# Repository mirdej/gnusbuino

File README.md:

gnusbuino
=========

arduino compatible version of the gnusb - open source usb sensor box

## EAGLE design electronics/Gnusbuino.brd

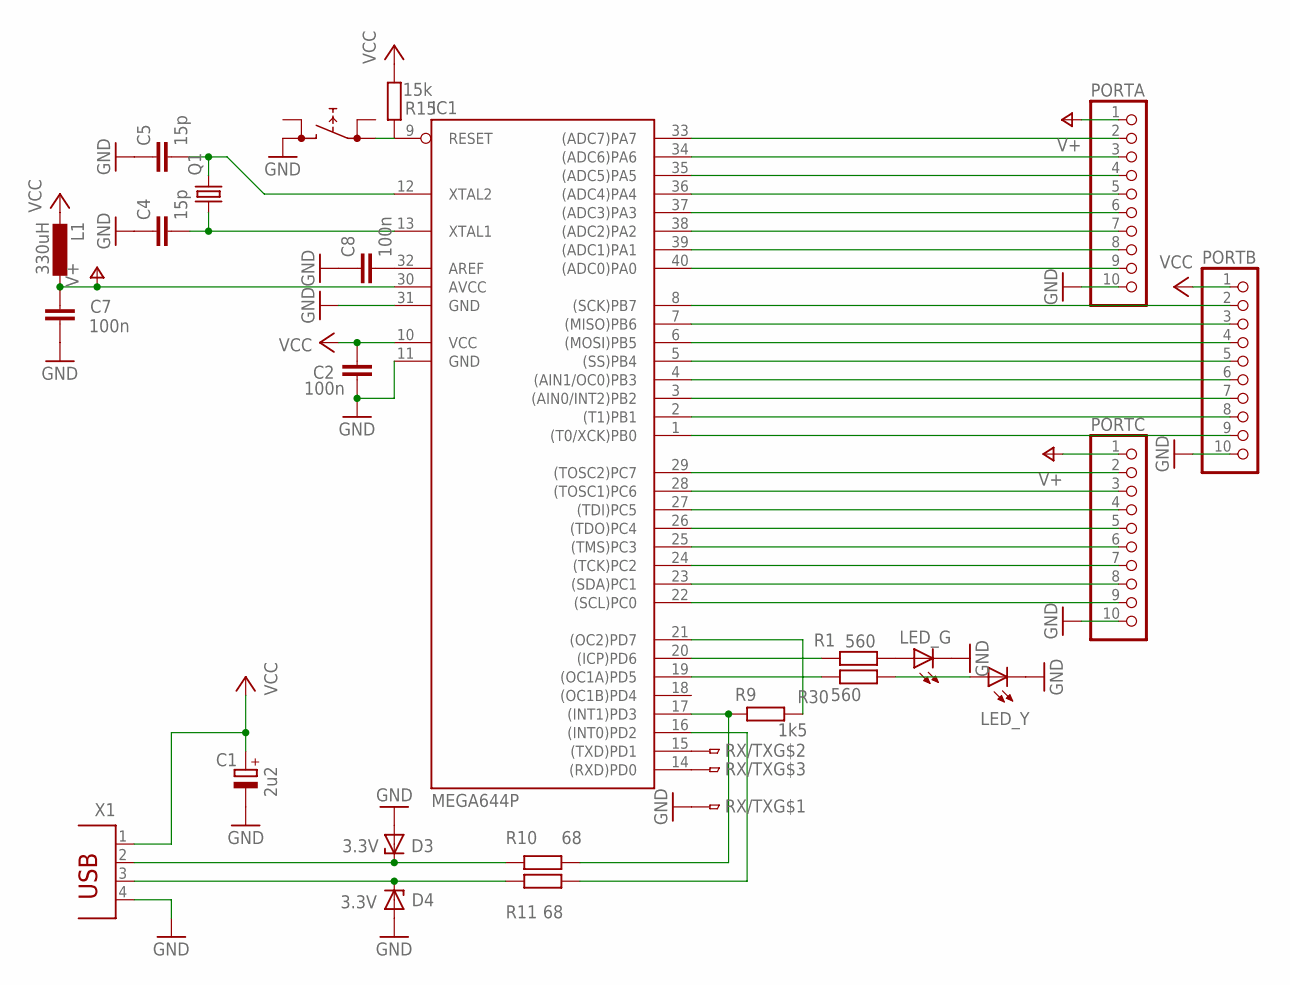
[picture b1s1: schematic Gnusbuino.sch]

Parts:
C1: 2u2; CT3528
C2, C7, C8: 100n; C0805
C4, C5: 15p; C1206
D3, D4: 3.3V; SOD80C
IC1: MEGA644P; DIL40
L1: 330uH; L1812
LED_G: LEDCHIPLED_1206; CHIPLED_1206
LED_Y: LEDCHIPLED_1206; CHIPLED_1206
PORTA: 10-PIN-SMD-2.54; 10PIN-SMD-2.54
PORTB: 10-PIN-SMD-2.54; 10PIN-SMD-2.54
PORTC: 10-PIN-SMD-2.54; 10PIN-SMD-2.54
Q1: CRYSTALHC49UP; HC49UP
R1, R30: 560; M1206
R9: 1k5; M1206
R10, R11: 68; M1206
R15: 15k; M1206
RESET: PRINTTASTER_SMD; SMD_SWITCH
RX/TX: 3PIN-SMD-2.54
X1: PN61729

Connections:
D+: D4.C, R11.1, X1.3
D-: D3.C, R10.1, X1.2
GND: C1.-, C2.2, C4.1, C5.1, C7.2, C8.1, D3.A, D4.A, IC1.11 (GND), IC1.31 (GND), LED_G.C, LED_Y.C, PORTA.10, PORTB.10, PORTC.10, RESET.BB (1), RX/TX.1, X1.4
MISO: IC1.7 ((MISO)PB6), PORTB.3
MOSI: IC1.6 ((MOSI)PB5), PORTB.4
unnamed: IC1.17 ((INT1)PD3), R9.2, R10.2
unnamed: IC1.9 (RESET), R15.1, RESET.AA (0)
unnamed: IC1.15 ((TXD)PD1), RX/TX.2
unnamed: IC1.14 ((RXD)PD0), RX/TX.3
unnamed: LED_G.A, R1.2
unnamed: C4.2, IC1.13 (XTAL1), Q1.1
unnamed: IC1.20 ((ICP)PD6), R1.1
unnamed: IC1.19 ((OC1A)PD5), R30.1
unnamed: LED_Y.A, R30.2
unnamed: C8.2, IC1.32 (AREF)
unnamed: IC1.33 ((ADC7)PA7), PORTA.2
unnamed: IC1.21 ((OC2)PD7), R9.1
unnamed: IC1.34 ((ADC6)PA6), PORTA.3
unnamed: IC1.35 ((ADC5)PA5), PORTA.4
unnamed: IC1.36 ((ADC4)PA4), PORTA.5
unnamed: IC1.37 ((ADC3)PA3), PORTA.6
unnamed: IC1.38 ((ADC2)PA2), PORTA.7
unnamed: IC1.39 ((ADC1)PA1), PORTA.8
unnamed: IC1.40 ((ADC0)PA0), PORTA.9
unnamed: IC1.4 ((AIN1/OC0)PB3), PORTB.6
unnamed: IC1.3 ((AIN0/INT2)PB2), PORTB.7
unnamed: IC1.2 ((T1)PB1), PORTB.8
unnamed: IC1.1 ((T0/XCK)PB0), PORTB.9
unnamed: IC1.16 ((INT0)PD2), R11.2
unnamed: IC1.29 ((TOSC2)PC7), PORTC.2
unnamed: IC1.28 ((TOSC1)PC6), PORTC.3
unnamed: IC1.27 ((TDI)PC5), PORTC.4
unnamed: IC1.26 ((TDO)PC4), PORTC.5
unnamed: IC1.25 ((TMS)PC3), PORTC.6
unnamed: IC1.24 ((TCK)PC2), PORTC.7
unnamed: IC1.23 ((SDA)PC1), PORTC.8
unnamed: IC1.22 ((SCL)PC0), PORTC.9
unnamed: C5.2, IC1.12 (XTAL2), Q1.2
SCK: IC1.8 ((SCK)PB7), PORTB.2
SS: IC1.5 ((SS)PB4), PORTB.5
V+: C7.1, IC1.30 (AVCC), L1.1, PORTA.1, PORTC.1
VCC: C1.+, C2.1, IC1.10 (VCC), L1.2, PORTB.1, R15.2, X1.1

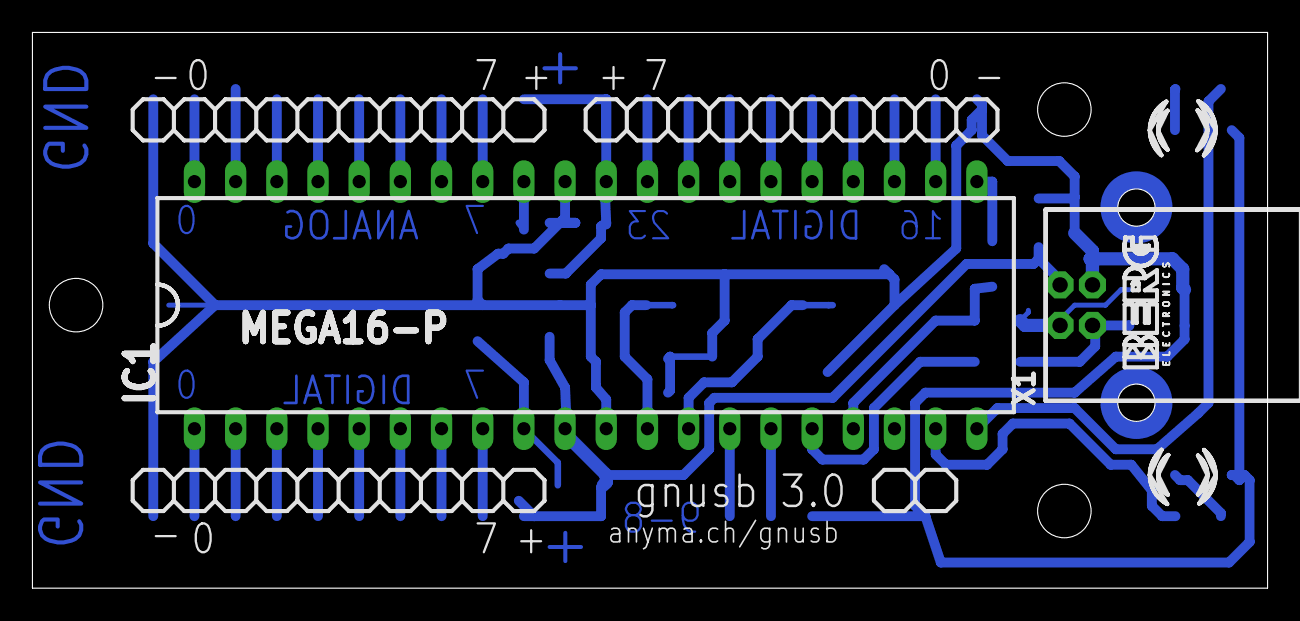
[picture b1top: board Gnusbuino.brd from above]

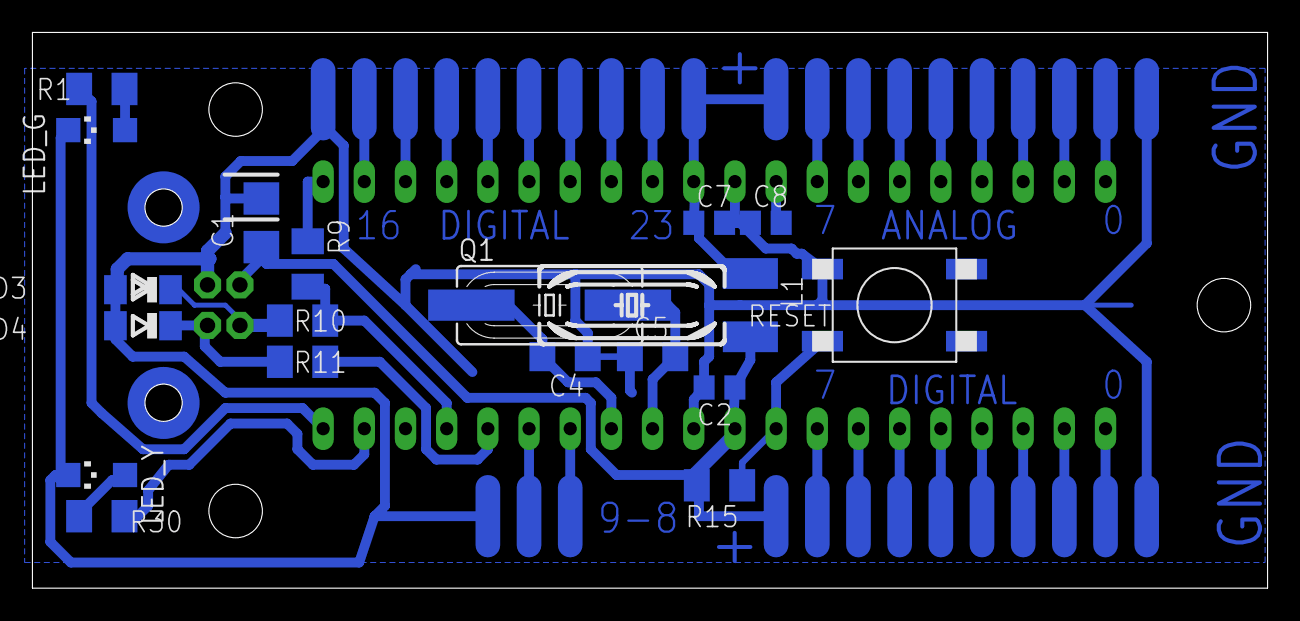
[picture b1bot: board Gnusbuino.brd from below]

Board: 2 copper layers, 76.2 x 34.3 mm, 25 parts (23 on the bottom side), 42 nets.

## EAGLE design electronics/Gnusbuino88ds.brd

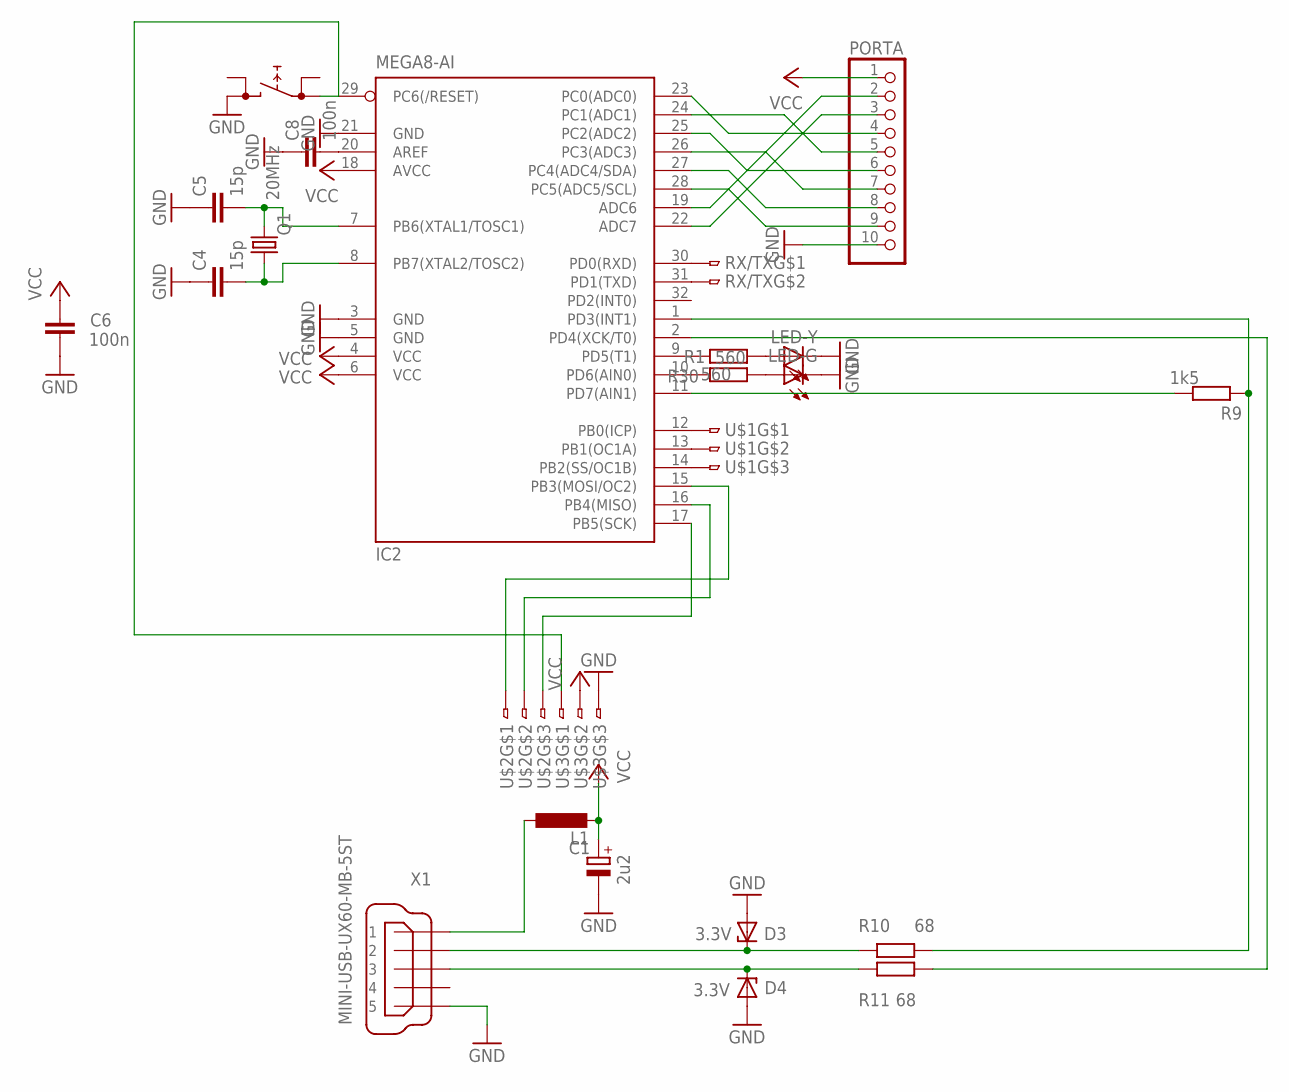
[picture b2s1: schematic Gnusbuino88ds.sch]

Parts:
C1: 2u2; CT3528
C4, C5: 15p; C1206
C6, C8: 100n; C0805
D3, D4: 3.3V; SOD80C
IC2: MEGA8-AI; TQFP32-08
L1: L-EUL3225M; L3225M
LED-G: LEDCHIPLED_1206; CHIPLED_1206
LED-Y: LEDCHIPLED_1206; CHIPLED_1206
PORTA: 10-PIN-SMD-2.54; 10PIN-SMD-2.54
Q1: 20MHz; HC49UP
R1, R30: 560; M1206
R9: 1k5; M1206
R10, R11: 68; M1206
RESET: PRINTTASTER_SMD; SMD_SWITCH
RX/TX: 3PIN-SMD-2.54
U$1, U$2, U$3: 3PIN-SMD-2.54
X1: MINI-USB-UX60-MB-5ST; UX60-MB-5ST

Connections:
D+: D4.C, R11.1, X1.3
D+1: IC2.2 (PD4(XCK/T0)), R11.2
D-: D3.C, R10.1, X1.2
GND: C1.-, C4.1, C5.1, C6.2, C8.1, D3.A, D4.A, IC2.3 (GND), IC2.5 (GND), IC2.21 (GND), LED-G.C, LED-Y.C, PORTA.10, RESET.BB (1), U$3.3, X1.5
unnamed: IC2.1 (PD3(INT1)), R9.2, R10.2
unnamed: IC2.29 (PC6(/RESET)), RESET.AA (0), U$3.1
unnamed: C8.2, IC2.20 (AREF)
unnamed: L1.1, X1.1
unnamed: LED-G.A, R1.2
unnamed: C4.2, IC2.8 (PB7(XTAL2/TOSC2)), Q1.1
unnamed: IC2.19 (ADC6), PORTA.2
unnamed: IC2.9 (PD5(T1)), R30.1
unnamed: LED-Y.A, R30.2
unnamed: IC2.10 (PD6(AIN0)), R1.1
unnamed: IC2.22 (ADC7), PORTA.3
unnamed: IC2.23 (PC0(ADC0)), PORTA.4
unnamed: IC2.11 (PD7(AIN1)), R9.1
unnamed: IC2.17 (PB5(SCK)), U$2.3
unnamed: IC2.24 (PC1(ADC1)), PORTA.5
unnamed: IC2.25 (PC2(ADC2)), PORTA.6
unnamed: IC2.26 (PC3(ADC3)), PORTA.7
unnamed: IC2.27 (PC4(ADC4/SDA)), PORTA.8
unnamed: IC2.28 (PC5(ADC5/SCL)), PORTA.9
unnamed: IC2.16 (PB4(MISO)), U$2.2
unnamed: IC2.15 (PB3(MOSI/OC2)), U$2.1
unnamed: IC2.12 (PB0(ICP)), U$1.1
unnamed: IC2.13 (PB1(OC1A)), U$1.2
unnamed: IC2.14 (PB2(SS/OC1B)), U$1.3
unnamed: IC2.30 (PD0(RXD)), RX/TX.1
unnamed: IC2.31 (PD1(TXD)), RX/TX.2
unnamed: C5.2, IC2.7 (PB6(XTAL1/TOSC1)), Q1.2
VCC: C1.+, C6.1, IC2.4 (VCC), IC2.6 (VCC), IC2.18 (AVCC), L1.2, PORTA.1, U$3.2

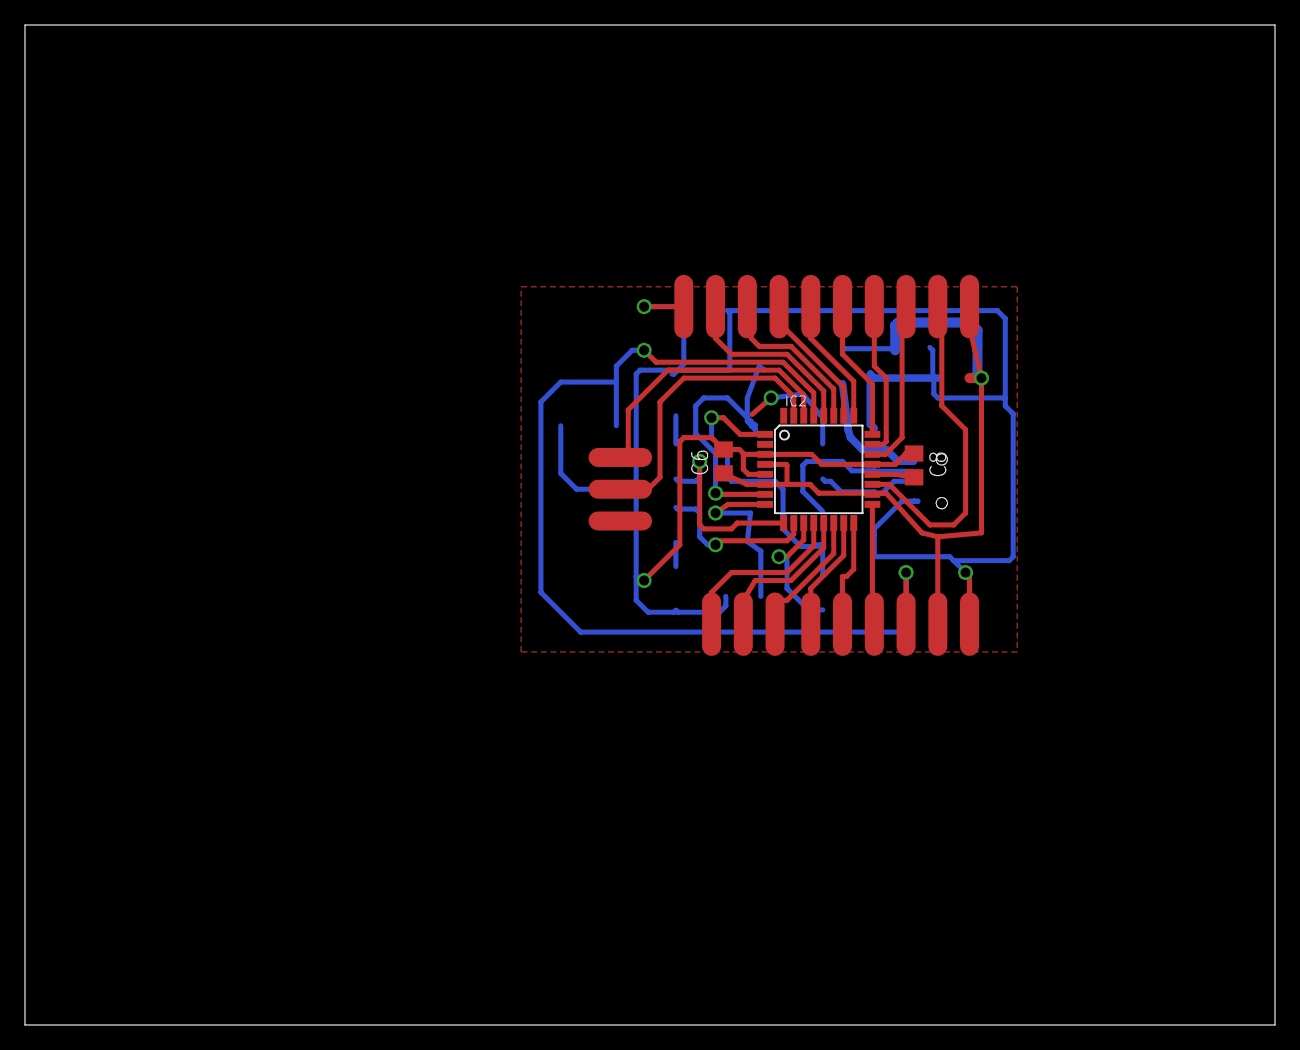
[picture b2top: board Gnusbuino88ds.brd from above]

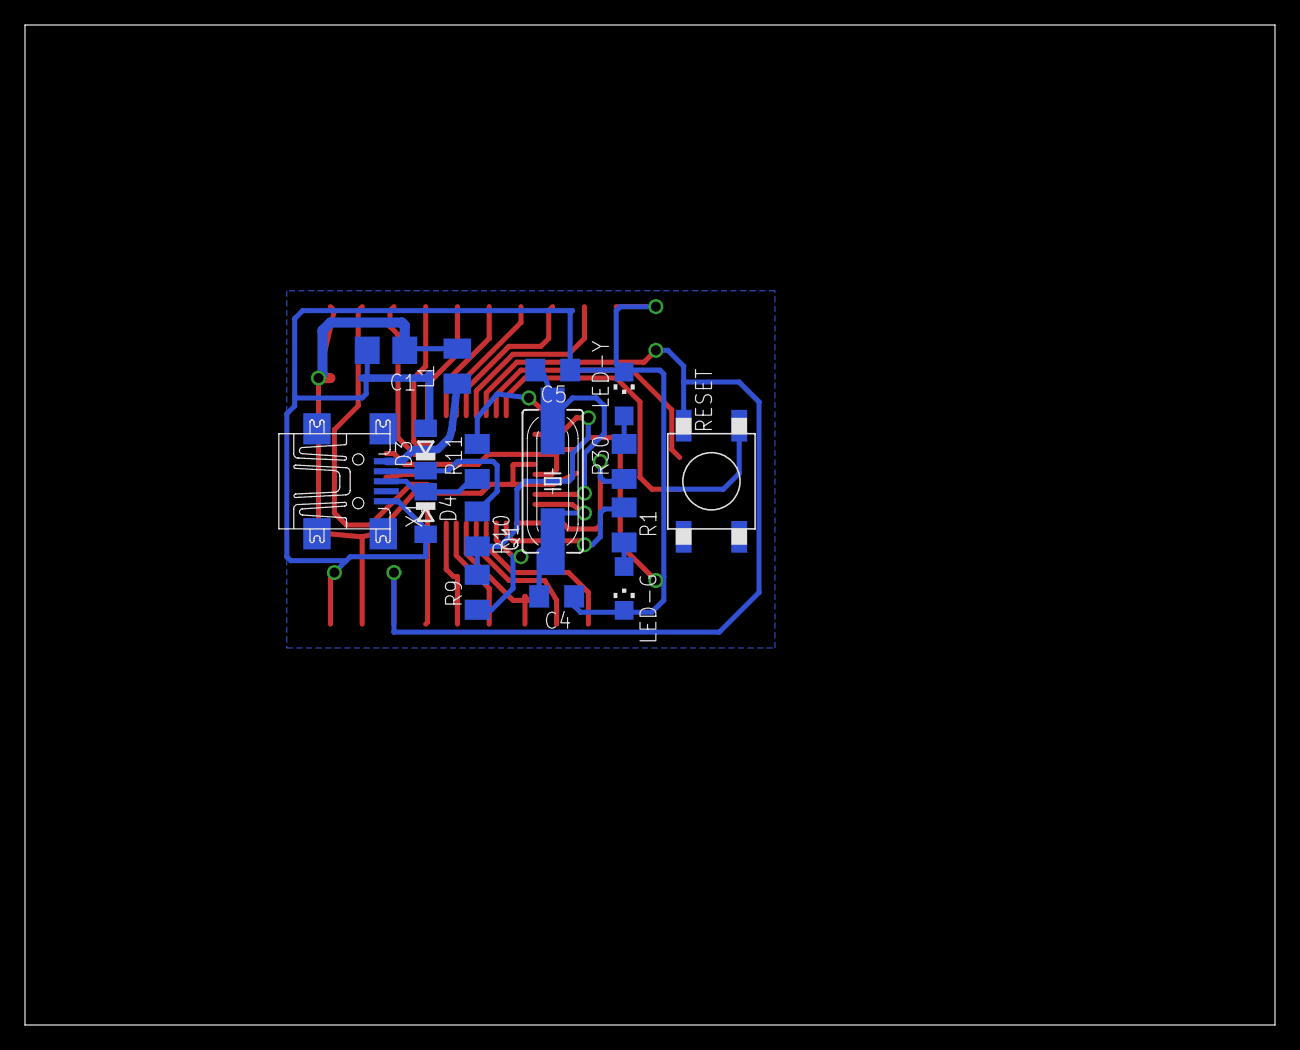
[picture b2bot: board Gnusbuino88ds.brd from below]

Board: 2 copper layers, 100.0 x 80.0 mm, 24 parts (16 on the bottom side), 32 nets.

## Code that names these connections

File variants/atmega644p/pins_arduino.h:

/*
  pins_arduino.h - Pin definition functions for ATMEGA644
  Part of Arduino - http://www.arduino.cc/

  Copyright (c) 2007 David A. Mellis
  2012 Michael Egger

  This library is free software; you can redistribute it and/or
  modify it under the terms of the GNU Lesser General Public
  License as published by the Free Software Foundation; either
  version 2.1 of the License, or (at your option) any later version.

  This library is distributed in the hope that it will be useful,
  but WITHOUT ANY WARRANTY; without even the implied warranty of
  MERCHANTABILITY or FITNESS FOR A PARTICULAR PURPOSE.  See the GNU
  Lesser General Public License for more details.

  You should have received a copy of the GNU Lesser General
  Public License along with this library; if not, write to the
  Free Software Foundation, Inc., 59 Temple Place, Suite 330,
  Boston, MA  02111-1307  USA

  $Id: wiring.h 249 2007-02-03 16:52:51Z mellis $
*/


// On the Sanguino board, digital pins are also used
// for the analog output (software PWM).  Analog input
// pins are a separate set.

// ATMEL ATMEGA644P / SANGUINO / GNUSBUINO
//
//                   +---\/---+
//  INT0 (D 0) PB0  1|        |40  PA0 (AI 0 / D31)
//  INT1 (D 1) PB1  2|        |39  PA1 (AI 1 / D30)
//  INT2 (D 2) PB2  3|        |38  PA2 (AI 2 / D29)
//   PWM (D 3) PB3  4|        |37  PA3 (AI 3 / D28)
//   PWM (D 4) PB4  5|        |36  PA4 (AI 4 / D27)
//  MOSI (D 5) PB5  6|        |35  PA5 (AI 5 / D26)
//  MISO (D 6) PB6  7|        |34  PA6 (AI 6 / D25)
//   SCK (D 7) PB7  8|        |33  PA7 (AI 7 / D24)
//             RST  9|        |32  AREF
//             VCC 10|        |31  GND 
//             GND 11|        |30  AVCC
//           XTAL2 12|        |29  PC7 (D 23)
//           XTAL1 13|        |28  PC6 (D 22)
//  RX  (D 8)  PD0 14|        |27  PC5 (D 21) TDI
//  TX  (D 9)  PD1 15|        |26  PC4 (D 20) TDO
//  USB (D 10) PD2 16|        |25  PC3 (D 19) TMS
//  USB (D 11) PD3 17|        |24  PC2 (D 18) TCK
//  PWM (D 12) PD4 18|        |23  PC1 (D 17) SDA
//  PWM (D 13) PD5 19|        |22  PC0 (D 16) SCL
//  PWM (D 14) PD6 20|        |21  PD7 (D 15) PWM
//                   +--------+
//

#ifndef Pins_Arduino_h
#define Pins_Arduino_h

#include <avr/pgmspace.h>

#define NUM_DIGITAL_PINS            24
#define NUM_ANALOG_INPUTS           8
#define analogInputToDigitalPin(p)  ((p < 8) ? (7 - p) + 24 : -1)
#define digitalPinHasPWM(p)         ((p) == 3  || (p) == 4 || (p) == 12 || (p) == 13 || (p) == 14)

static const uint8_t SS   = 4;
static const uint8_t MOSI = 5;
static const uint8_t MISO = 6;
static const uint8_t SCK  = 7;

static const uint8_t SDA = 17;
static const uint8_t SCL = 16;
static const uint8_t LED_BUILTIN = 13;

static const uint8_t A0 = 0;
static const uint8_t A1 = 1;
static const uint8_t A2 = 2;
static const uint8_t A3 = 3;
static const uint8_t A4 = 4;
static const uint8_t A5 = 5;
static const uint8_t A6 = 6;
static const uint8_t A7 = 7;



#ifdef ARDUINO_MAIN
//ok from here on down.......

#define PA 1
#define PB 2
#define PC 3
#define PD 4

const uint16_t PROGMEM port_to_mode_PGM[] = {
	NOT_A_PORT,
        (uint8_t) &DDRA,
	(uint8_t) &DDRB,
	(uint8_t) &DDRC,
	(uint8_t) &DDRD,
};

const uint16_t PROGMEM port_to_output_PGM[] = {
	NOT_A_PORT,
	(uint8_t) &PORTA,
	(uint8_t) &PORTB,
	(uint8_t) &PORTC,
	(uint8_t) &PORTD,
};

const uint16_t PROGMEM port_to_input_PGM[] = {
	NOT_A_PORT,
	(uint8_t) &PINA,
	(uint8_t) &PINB,
	(uint8_t) &PINC,
	(uint8_t) &PIND,
};

const uint8_t PROGMEM digital_pin_to_port_PGM[] = {
	// PORTLIST		
	// -------------------------------------------		
	PB, /* 0 */
	PB,
	PB,
	PB,
	PB,
	PB,
	PB,
	PB,
	PD, /* 8 */
	PD,
	PD,
	PD,
	PD,
	PD,
	PD,
	PD,
	PC, /* 16 */
	PC,
	PC,
	PC,
	PC,
	PC,
   	PC,
	PC,
	PA, /* 24 */
	PA,
	PA,
	PA,
	PA,
	PA,
	PA,
	PA  /* 31 */
};

//ok
const uint8_t PROGMEM digital_pin_to_bit_mask_PGM[] = {
	// PIN IN PORT		
	// -------------------------------------------		
	_BV(0), /* 0, port B */
	_BV(1),
	_BV(2),
	_BV(3),
	_BV(4),
	_BV(5),
	_BV(6),
	_BV(7),
	_BV(0), /* 8, port D */
	_BV(1),
	_BV(2),
	_BV(3),
	_BV(4),
	_BV(5),
	_BV(6),
	_BV(7),
	_BV(0), /* 16, port C */
	_BV(1),
	_BV(2),
	_BV(3),
	_BV(4),
	_BV(5),
	_BV(6),
	_BV(7),
	_BV(7), /* 24, port A */
	_BV(6),
	_BV(5),
	_BV(4),
	_BV(3),
	_BV(2),
	_BV(1),
	_BV(0)
};

//ok
const uint8_t PROGMEM digital_pin_to_timer_PGM[] = {
	// TIMERS		
	// -------------------------------------------		
	NOT_ON_TIMER, 	/* 0  - PB0 */
	NOT_ON_TIMER, 	/* 1  - PB1 */
	NOT_ON_TIMER, 	/* 2  - PB2 */
	TIMER0A,     	/* 3  - PB3 */
	TIMER0B, 		/* 4  - PB4 */
	NOT_ON_TIMER, 	/* 5  - PB5 */
	NOT_ON_TIMER, 	/* 6  - PB6 */
	NOT_ON_TIMER,	/* 7  - PB7 */
	NOT_ON_TIMER, 	/* 8  - PD0 */
	NOT_ON_TIMER, 	/* 9  - PD1 */
	NOT_ON_TIMER, 	/* 10 - PD2 */
	NOT_ON_TIMER, 	/* 11 - PD3 */
	TIMER1B,     	/* 12 - PD4 */
	TIMER1A,     	/* 13 - PD5 */
	TIMER2B,     	/* 14 - PD6 */
	TIMER2A,     	/* 15 - PD7 */
	NOT_ON_TIMER, 	/* 16 - PC0 */
	NOT_ON_TIMER,   /* 17 - PC1 */
	NOT_ON_TIMER,   /* 18 - PC2 */
	NOT_ON_TIMER,   /* 19 - PC3 */
	NOT_ON_TIMER,   /* 20 - PC4 */
	NOT_ON_TIMER,   /* 21 - PC5 */
	NOT_ON_TIMER,   /* 22 - PC6 */
	NOT_ON_TIMER,   /* 23 - PC7 */
	NOT_ON_TIMER,   /* 24 - PA0 */
	NOT_ON_TIMER,   /* 25 - PA1 */
	NOT_ON_TIMER,   /* 26 - PA2 */
	NOT_ON_TIMER,   /* 27 - PA3 */
	NOT_ON_TIMER,   /* 28 - PA4 */
	NOT_ON_TIMER,   /* 29 - PA5 */
	NOT_ON_TIMER,   /* 30 - PA6 */
	NOT_ON_TIMER   /* 31 - PA7 */

};

#endif

#endif

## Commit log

2013-12-01 initial import of version 2012-12 from a svn export from sourceforge
2013-12-03 added atmega644 bootloader hex file
2013-12-03 fixed library include
2013-12-03 fixed another include
2013-12-03 updated pdf
2013-12-03 think i fixed bug where midi queue would fill up because only sevided once every millisecond
2014-06-01 atmega88 version
2014-06-01 add files*
2015-11-02 fixed p error in gnusbuino variant
2015-11-16 added support for analogReference()
2015-11-17 recompiled bootloader. last version seemed to stay in bootloader on reconnect. needed to upload several times from arduino before program started working. no idea why...
2015-11-30 fixed backannotation error
